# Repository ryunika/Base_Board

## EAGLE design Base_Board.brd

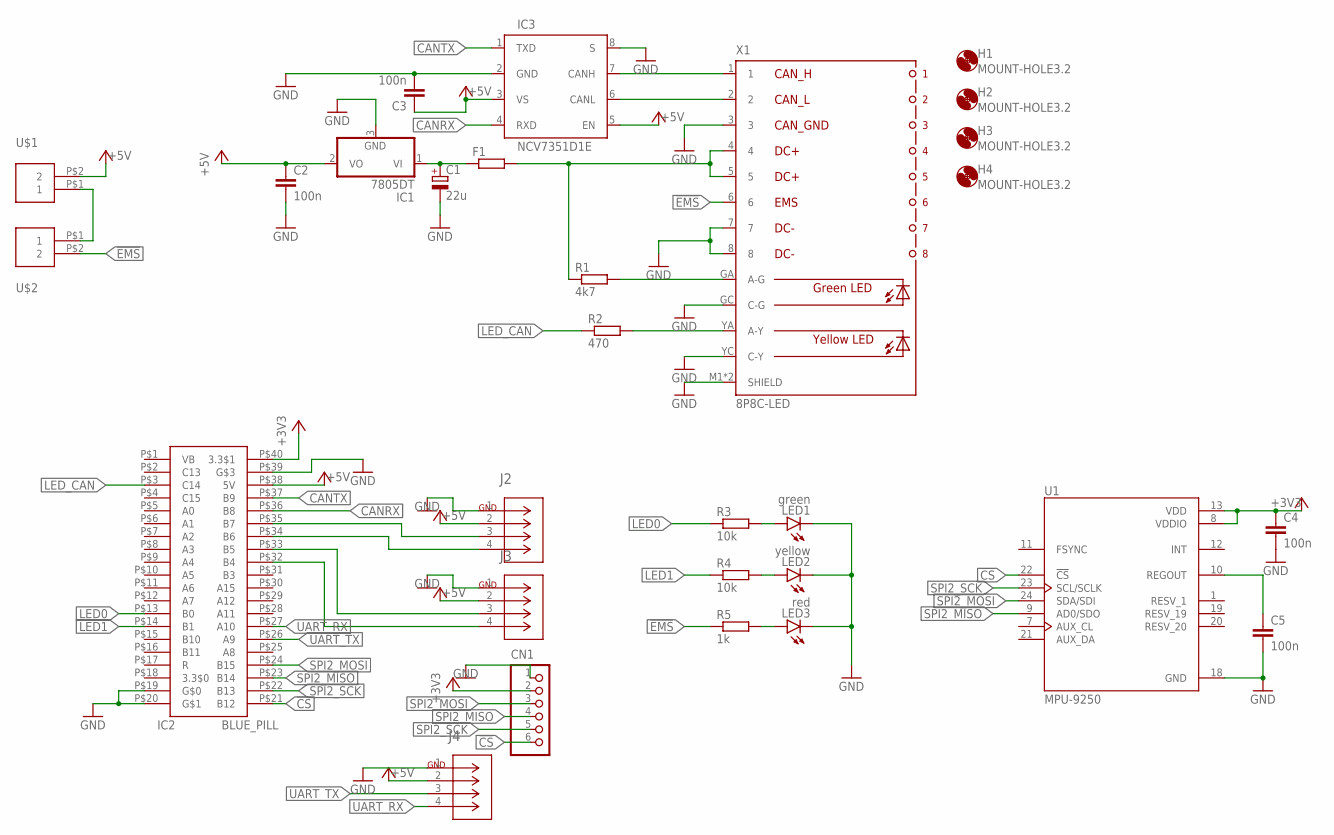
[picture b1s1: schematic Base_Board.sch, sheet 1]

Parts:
C1: 22u; E2,5-5
C2, C3, C4, C5: 100n; C0603
CN1: S6B-XH-A
F1: R-EU_R1206; R1206
H1, H2, H3, H4: MOUNT-HOLE3.2; 3,2
IC1: 7805DT; TO252
IC2: BLUE_PILL
IC3: NCV7351D1E; SO08
J2, J3, J4: EP2.5-4-SIDE; CONN4_1744426-4
LED1: green; CHIPLED_0805
LED2: yellow; CHIPLED_0805
LED3: red; CHIPLED_0805
R1: 4k7; R0603
R2: 470; R0603
R3, R4: 10k; R0603
R5: 1k; R0603
U1: MPU-9250; QFN40P300X300X105-24N
U$1, U$2: XH-2-STRAIGHT; CON-XH-2-STRAIGHT
X1: 8P8C-LED

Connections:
!CS: CN1.6, IC2.P$21 (B12), U1.22 (!CS)
!EMS: R5.1, U$2.P$2 (2), X1.6
+3V3: C4.1, CN1.2, IC2.P$40 (3.3$1), U1.8 (VDDIO), U1.13 (VDD)
+5V: C2.1, C3.1, IC1.2 (VO), IC2.P$38 (5V), IC3.3 (VS), IC3.5 (EN), J2.2, J3.2, J4.2, U$1.P$2 (2)
CANRX: IC2.P$36 (B8), IC3.4 (RXD)
CANTX: IC2.P$37 (B9), IC3.1 (TXD)
GND: C1.-, C2.2, C3.2, C4.2, C5.2, CN1.1, IC1.3 (GND), IC2.P$19, IC2.P$20, IC2.P$39, IC3.2 (GND), IC3.8 (S), J2.1, J3.1, J4.1, LED1.C, LED2.C, LED3.C, U1.18 (GND), X1.3, X1.7, X1.8, X1.GC (C-G), X1.M1 (SHIELD), X1.M2 (SHIELD), X1.YC (C-Y)
LED0: IC2.P$13 (B0), R3.1
LED1: IC2.P$14 (B1), R4.1
LED_CAN: IC2.P$3 (C14), R2.1
unnamed: R1.2, X1.GA (A-G)
unnamed: F1.2, R1.1, X1.4, X1.5
unnamed: C1.+, F1.1, IC1.1 (VI)
unnamed: IC3.7 (CANH), X1.1
unnamed: IC3.6 (CANL), X1.2
unnamed: IC2.P$32 (B4), J3.4
unnamed: IC2.P$33 (B5), J3.3
unnamed: IC2.P$34 (B6), J2.4
unnamed: R2.2, X1.YA (A-Y)
unnamed: IC2.P$35 (B7), J2.3
unnamed: U$1.P$1 (1), U$2.P$1 (1)
unnamed: LED1.A, R3.2
unnamed: LED2.A, R4.2
unnamed: LED3.A, R5.2
unnamed: C5.1, U1.10 (REGOUT)
SPI2_MISO: CN1.4, IC2.P$23 (B14), U1.9 (AD0/SDO)
SPI2_MOSI: CN1.3, IC2.P$24 (B15), U1.24 (SDA/SDI)
SPI2_SCK: CN1.5, IC2.P$22 (B13), U1.23 (SCL/SCLK)
UART_RX: IC2.P$27 (A10), J4.4
UART_TX: IC2.P$26 (A9), J4.3

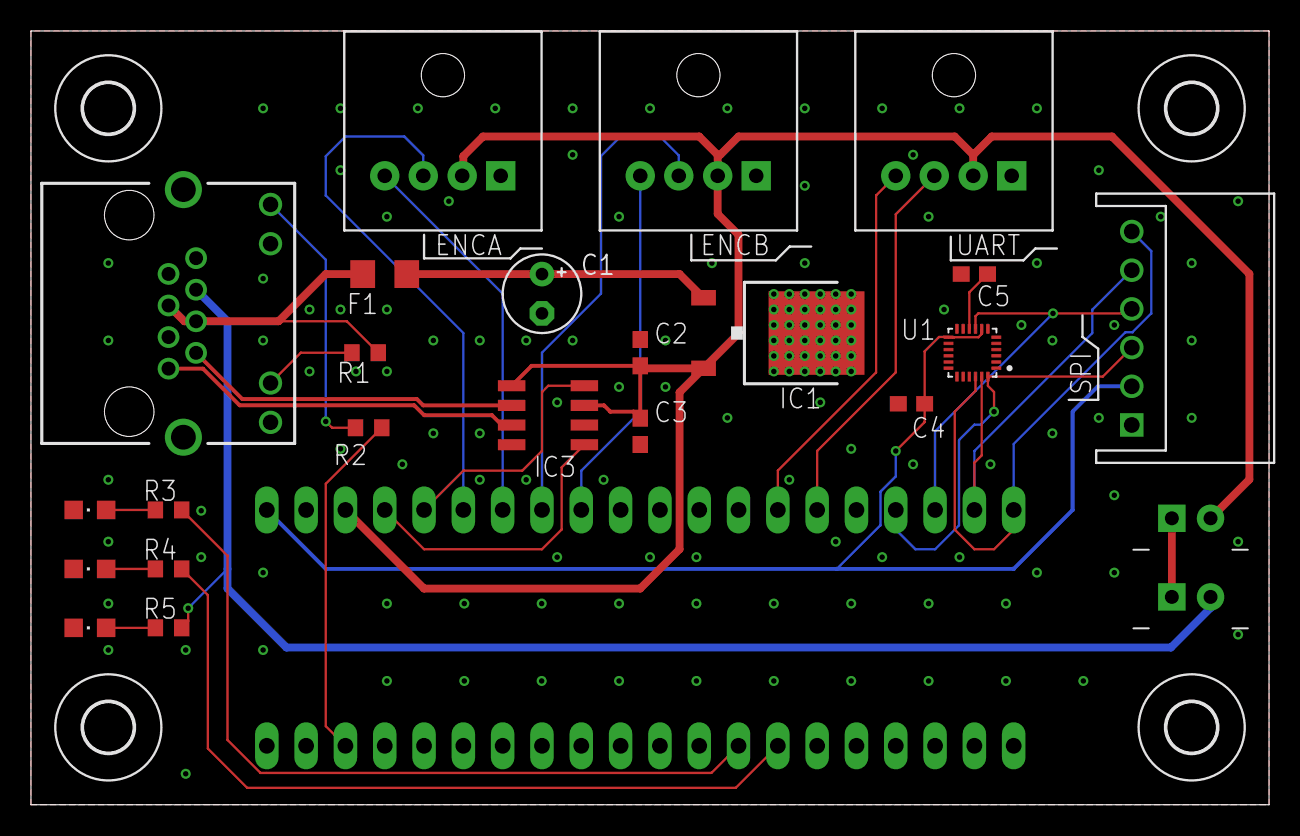
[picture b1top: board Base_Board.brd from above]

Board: 2 copper layers, 80.0 x 50.0 mm, 29 parts (0 on the bottom side), 30 nets.
